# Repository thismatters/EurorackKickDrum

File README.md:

# Kick Drum

The circuit here is an implementation the circuit in the [Moritz Klien kick drum video](https://www.youtube.com/watch?v=yz37Yz315eU) with all of the trappings to make it a proper module. The aforementioned video is extremely good and deserves a watch (along with all their other content, top notch). While the [Erica Synths kit](https://www.ericasynths.lv/shop/diy-kits-1/edu-diy-kick-drum/) has 7 knobs I have limited myself to 4 knobs: Decay, Pitch, Distortion, and Tone. The other 3 knobs are be present as screw-turn potentiometers accessible from the front panel for retuning the module.

The KiCAD project here uses the library/footprints [found in my companion repo](https://github.com/thismatters/EurorackKiCAD).

## Width

6hp on a standard 3U rack.

## Inputs

3 Jacks
- Gate
- Accent CV
- Pitch CV

4 Knobs:
- Decay
- Distortion
- Tone
- Pitch

3 Screw Pots (accessible from front):
- Tune Decay
- Tune Depth
- Max Pitch CV

## Outputs

1 Jack for audio output.

## Vendors

There are part numbers in the [BOM](kick-drum.csv) for many of the parts (not for basic passives though) at the following vendors:

* [Mouser](https://www.mouser.com): Needs no introduction. Get your ICs from here (or [digikey](https://www.digikey.com)).
* [Tayda Electronics](https://www.taydaelectronics.com/): Good supplier for passive components; audio jacks, and potentiometers. Their audio jacks are slightly smaller than the thonkiconn from thonk.
* [Love My Switches](https://lovemyswitches.com/): Has [really good knobs](https://lovemyswitches.com/anodized-aluminum-knob-the-lo-fi-1-4-smooth-shaft-12-5mm-od/) to go on those potentiometers!
* [OSHPark](https://oshpark.com/): Fast and (relatively) cheap PCB manufacturer. Prototype run pending.

## Changelog

### V1
- [x] Fixed critical bug which shorted the bridged-T to the Tune depth chain.
- [x] Fixed footprint for Q2

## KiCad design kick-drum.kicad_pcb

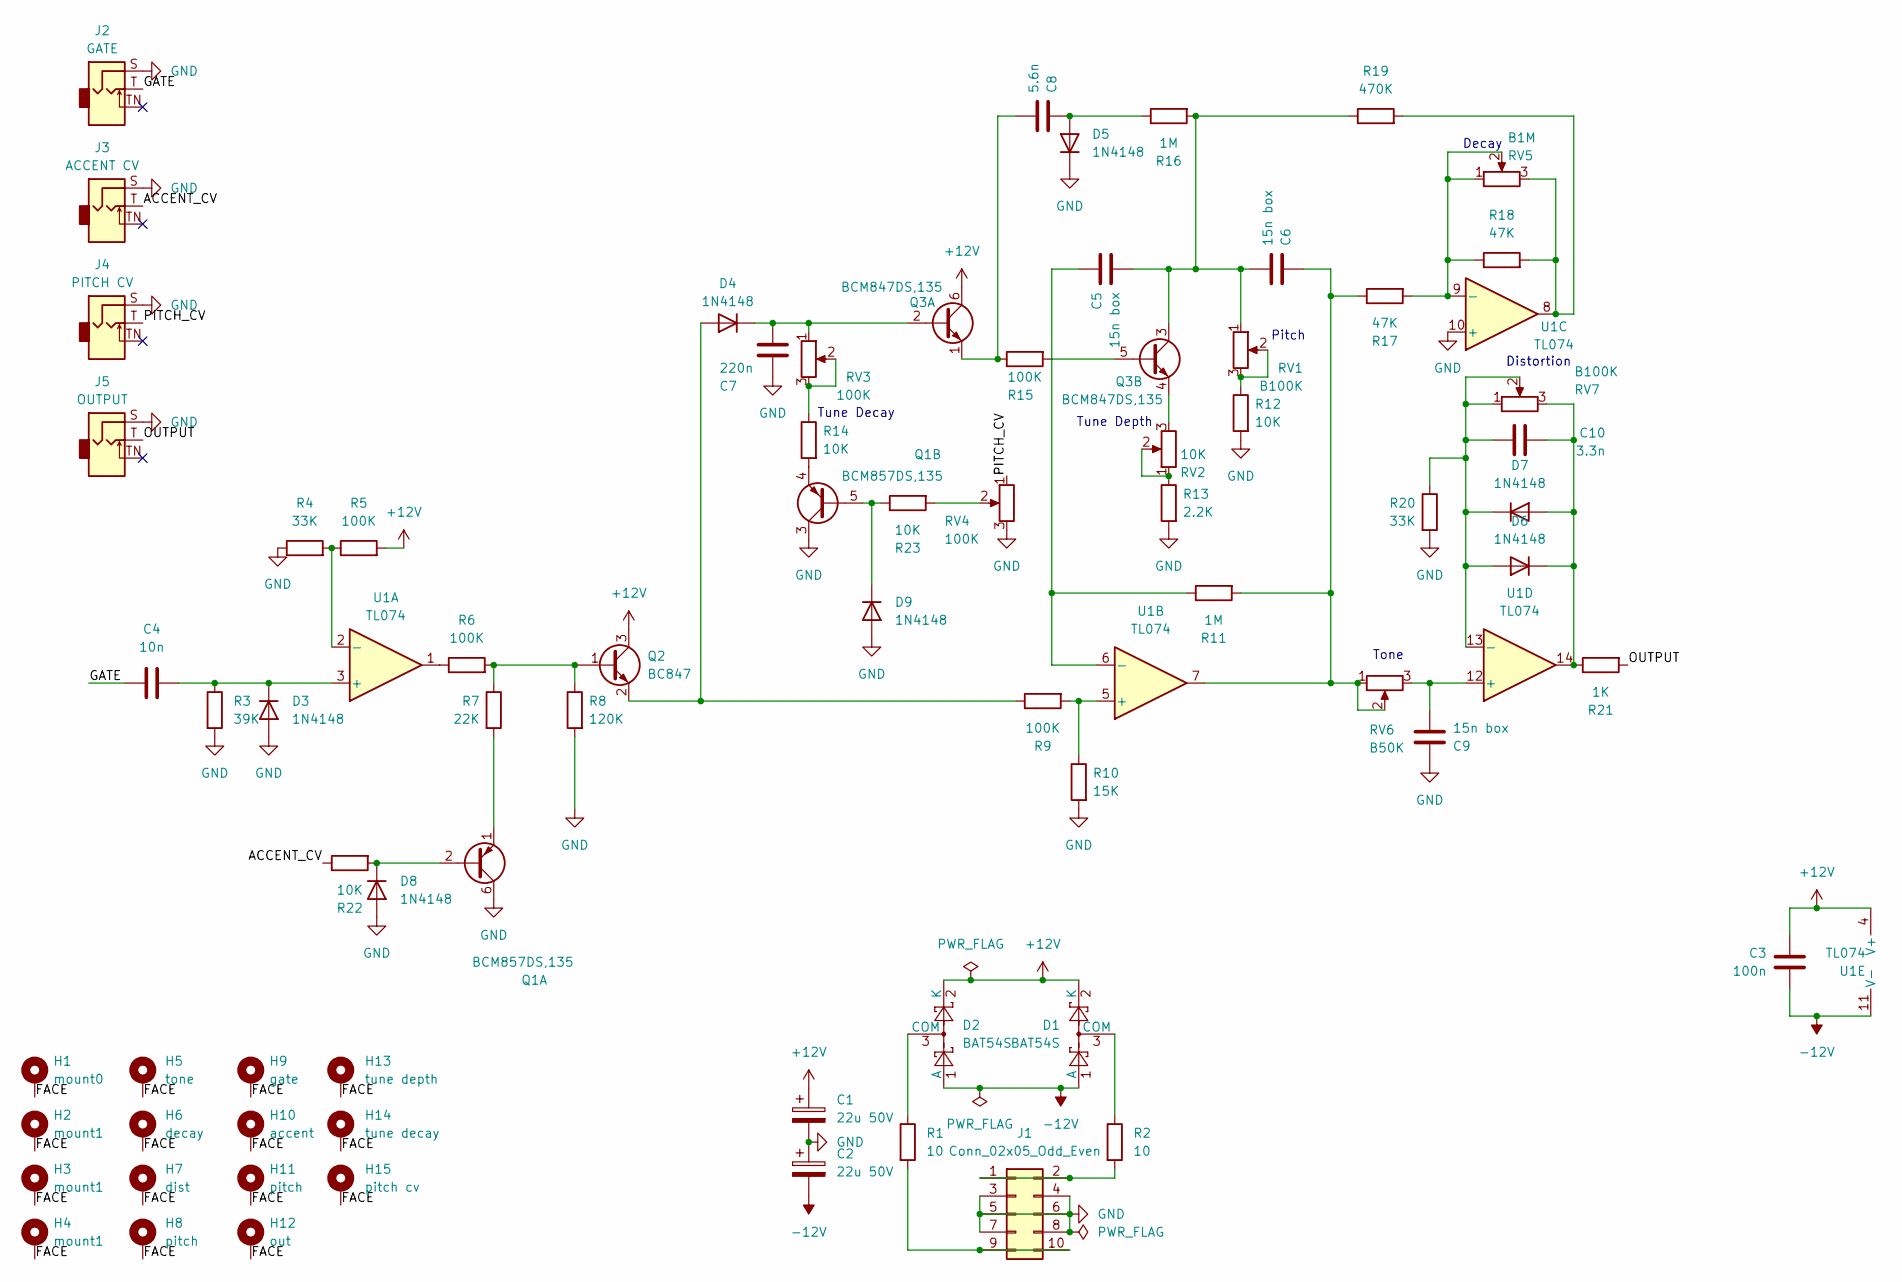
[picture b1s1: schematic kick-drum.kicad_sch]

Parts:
C1, C2: 22u 50V; CP_Radial_D5.0mm_P2.50mm
C3: 100n; C_0805_2012Metric
C4: 10n; C_0805_2012Metric
C5, C6, C9: 15n box; C_Rect_L7.2mm_W3.5mm_P5.00mm_FKS2_FKP2_MKS2_MKP2
C7: 220n; C_0805_2012Metric
C8: 5.6n; C_0805_2012Metric
C10: 3.3n; C_0805_2012Metric
D1, D2: BAT54S; SOT-23; PartNum 863-BAT54SLT1G
D3, D4, D5, D6, D7, D8, D9: 1N4148; D_SOD-323_HandSoldering
H1: mount0; Mech-MountingHole
H2, H3, H4: mount1; Mech-MountingHole
H5: tone; Mech-Potentiometer-Hole_level
H6: decay; Mech-Potentiometer-Hole_level
H7: dist; Mech-Potentiometer-Hole_level
H8: pitch; Mech-Potentiometer-Hole_level
H9: gate; Mech-AudioJack-Hole-Input-Gate
H10: accent; Mech-AudioJack-Hole-Input-CV
H11: pitch; Mech-AudioJack-Hole-Input-CV
H12: out; Mech-AudioJack-Hole-Output
H13: tune depth; Mech-LED-Hole-3mm
H14: tune decay; Mech-LED-Hole-3mm
H15: pitch cv; Mech-LED-Hole-3mm
J1: Conn_02x05_Odd_Even; PinHeader_2x05_P2.54mm_Vertical; PartNum A-2939
J2: GATE; AudioJack2_Tayda_A-2566; PartNum A-2566
J3: ACCENT CV; AudioJack2_Tayda_A-2566; PartNum A-2566
J4: PITCH CV; AudioJack2_Tayda_A-2566; PartNum A-2566
J5: OUTPUT; AudioJack2_Tayda_A-2566; PartNum A-2566
Q1: BCM857DS,135; TSOP-6_1.65x3.05mm_P0.95mm
Q2: BC847; SOT-23; PartNum 621-BC847C-13-F
Q3: BCM847DS,135; TSOP-6_1.65x3.05mm_P0.95mm
R1, R2: 10; R_0805_2012Metric
R3: 39K; R_0805_2012Metric
R4, R20: 33K; R_0805_2012Metric
R5, R6, R9, R15: 100K; R_0805_2012Metric
R7: 22K; R_0805_2012Metric
R8: 120K; R_0805_2012Metric
R10: 15K; R_0805_2012Metric
R11, R16: 1M; R_0805_2012Metric
R12, R14, R22, R23: 10K; R_0805_2012Metric
R13: 2.2K; R_0805_2012Metric
R17, R18: 47K; R_0805_2012Metric
R19: 470K; R_0805_2012Metric
R21: 1K; R_0805_2012Metric
RV1, RV7: B100K; Potentiometer_RV16AF-41-15R1
RV2: 10K; Potentiometer_Bourns_3296W_Vertical
RV3, RV4: 100K; Potentiometer_Bourns_3296W_Vertical
RV5: B1M; Potentiometer_RV16AF-41-15R1
RV6: B50K; Potentiometer_RV16AF-41-15R1
U1: TL074; SOIC-14_3.9x8.7mm_P1.27mm; PartNum 595-TL074CDR

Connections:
+12V: C1.1, C3.1, D1.2 (K), D2.2 (K), Q2.3 (C), Q3.6 (C1), R5.2, U1.4 (V+)
-12V: C2.2, C3.2, D1.1 (A), D2.1 (A), U1.11 (V-)
/ACCENT_CV: J3.T, R22.1
/FACE: H1.1, H2.1, H3.1, H4.1, H5.1, H6.1, H7.1, H8.1, H9.1, H10.1, H11.1, H12.1, H13.1, H14.1, H15.1
/GATE: C4.1, J2.T
/OUTPUT: J5.T, R21.2
/PITCH_CV: J4.T, RV4.1
GND: C1.2, C2.1, C7.1, C9.1, D3.2 (A), D5.1 (K), D8.2 (A), D9.2 (A), J1.3, J1.4, J1.5, J1.6, J1.7, J1.8, J2.S, J3.S, J4.S, J5.S, Q1.3 (C2), Q1.6 (C1), R3.2, R4.1, R8.2, R10.2, R12.2, R13.2, R20.2, RV4.3, U1.10 (+)
unnamed: C6.1, R11.2, R17.1, RV6.1, RV6.2, U1.7
unnamed: D1.3 (COM), R2.1
unnamed: D2.3 (COM), R1.1
unnamed: C4.2, D3.1 (K), R3.1, U1.3 (+)
unnamed: D4.2 (A), Q2.2 (E), R9.1
unnamed: C7.2, D4.1 (K), Q3.2 (B1), RV3.1
unnamed: C8.1, D5.2 (A), R16.1
unnamed: C10.2, D6.2 (A), D7.1 (K), R20.1, RV7.1, RV7.2, U1.13 (-)
unnamed: C10.1, D6.1 (K), D7.2 (A), R21.1, RV7.3, U1.14
unnamed: D8.1 (K), Q1.2 (B1), R22.2
unnamed: D9.1 (K), Q1.5 (B2), R23.1
unnamed: J1.1, J1.2, R2.2
unnamed: J1.9, J1.10, R1.2
unnamed: Q1.1 (E1), R7.2
unnamed: Q1.4 (E2), R14.2
unnamed: Q2.1 (B), R6.2, R7.1, R8.1
unnamed: C8.2, Q3.1 (E1), R15.1
unnamed: Q3.5 (B2), R15.2
unnamed: C5.2, C6.2, Q3.3 (C2), R16.2, R19.1, RV1.1
unnamed: Q3.4 (E2), RV2.3
unnamed: R6.1, U1.1
unnamed: R12.1, RV1.2, RV1.3
unnamed: R13.1, RV2.1, RV2.2
unnamed: R14.1, RV3.2, RV3.3
unnamed: R18.2, R19.2, RV5.3, U1.8
unnamed: R23.2, RV4.2
unnamed: R4.2, R5.1, U1.2 (-)
unnamed: R9.2, R10.1, U1.5 (+)
unnamed: C5.1, R11.1, U1.6 (-)
unnamed: R17.2, R18.1, RV5.1, RV5.2, U1.9 (-)
unnamed: C9.2, RV6.3, U1.12 (+)

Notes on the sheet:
Tune Decay
Tune Depth
Distortion
Pitch
Tone
Decay

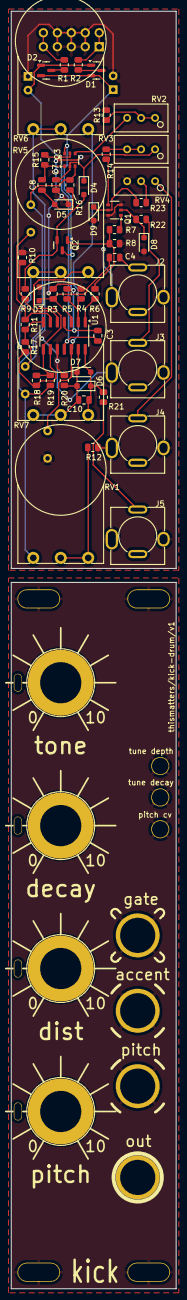
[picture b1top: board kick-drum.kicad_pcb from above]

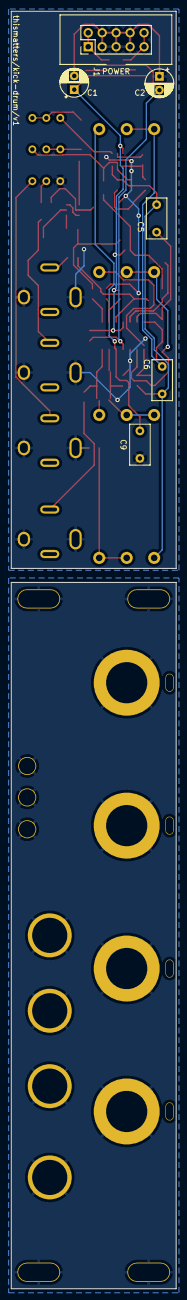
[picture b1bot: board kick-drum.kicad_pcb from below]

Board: 2 copper layers, 30.0 x 232.4 mm, 73 parts (6 on the bottom side), 39 nets.

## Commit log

2025-12-29 update footprints
2025-12-31 update 15n caps to box type
2025-12-31 bill of materials updates
2026-01-06 prelim board layout
2026-01-11 v0 ready
2026-01-31 prefab checklist v0
2026-02-01 adding CV input protection
2026-02-01 update PCB for input protection
2026-04-19 v1 ready
2026-04-19 include new schematic
